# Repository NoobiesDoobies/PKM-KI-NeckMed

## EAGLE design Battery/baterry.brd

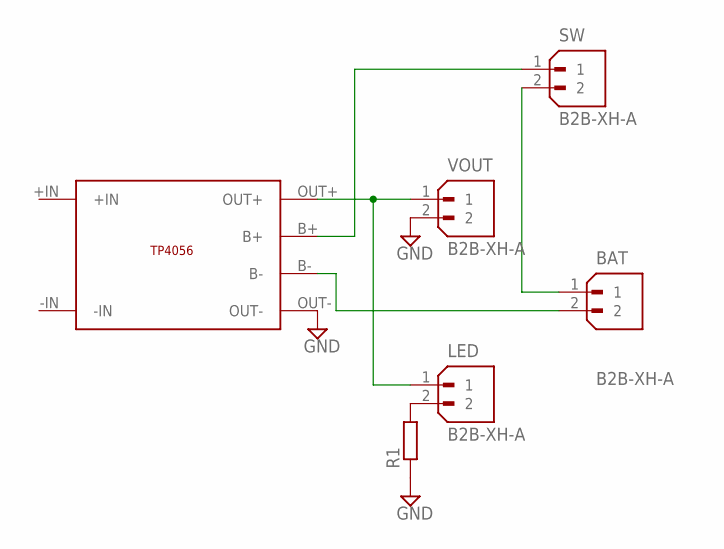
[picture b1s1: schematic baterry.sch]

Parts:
BAT: B2B-XH-A; JST_B2B-XH-A
LED: B2B-XH-A; JST_B2B-XH-A
R1: R-EU_0207/10; 0207/10
SW: B2B-XH-A; JST_B2B-XH-A
U$1: TP4056
VOUT: B2B-XH-A; JST_B2B-XH-A

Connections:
GND: R1.1, U$1.OUT-, VOUT.2
unnamed: LED.2, R1.2
unnamed: BAT.1, SW.2
unnamed: LED.1, U$1.OUT+, VOUT.1
unnamed: SW.1, U$1.B+
unnamed: BAT.2, U$1.B-

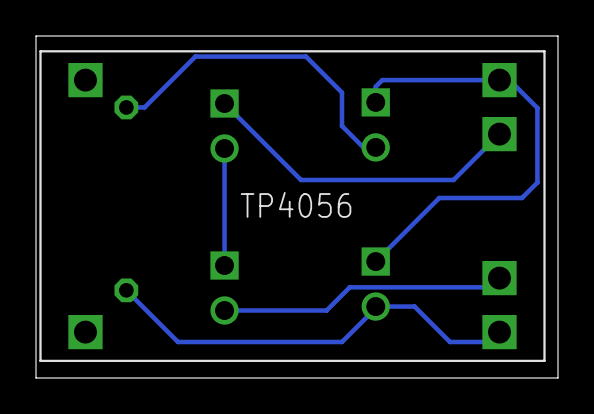
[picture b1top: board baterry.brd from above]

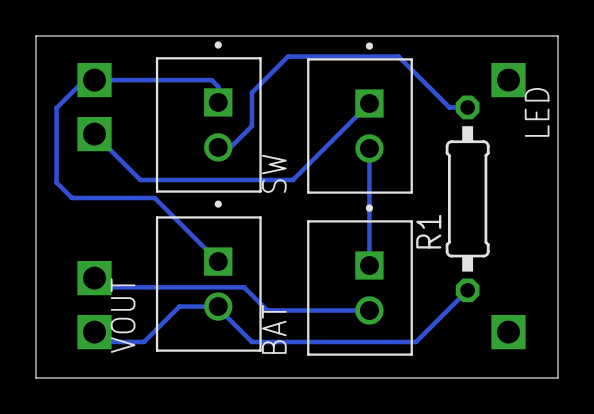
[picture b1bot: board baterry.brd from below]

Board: 2 copper layers, 29.0 x 19.0 mm, 6 parts (5 on the bottom side), 6 nets.

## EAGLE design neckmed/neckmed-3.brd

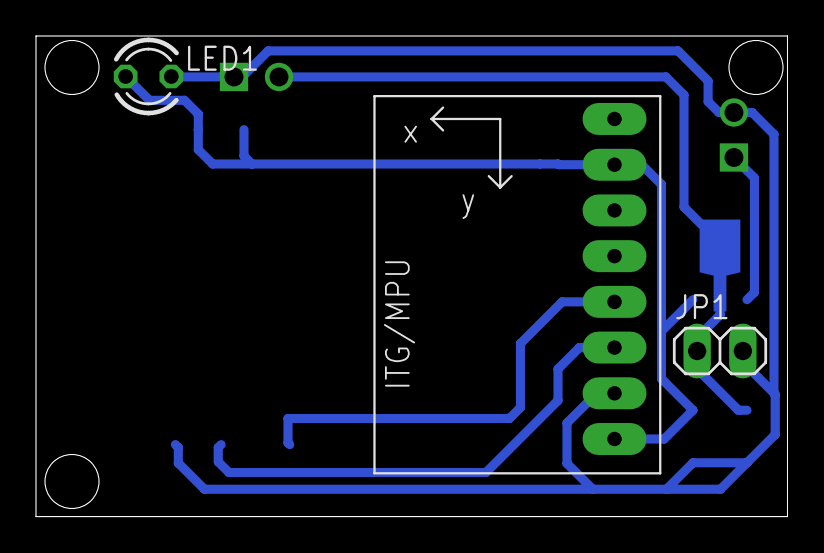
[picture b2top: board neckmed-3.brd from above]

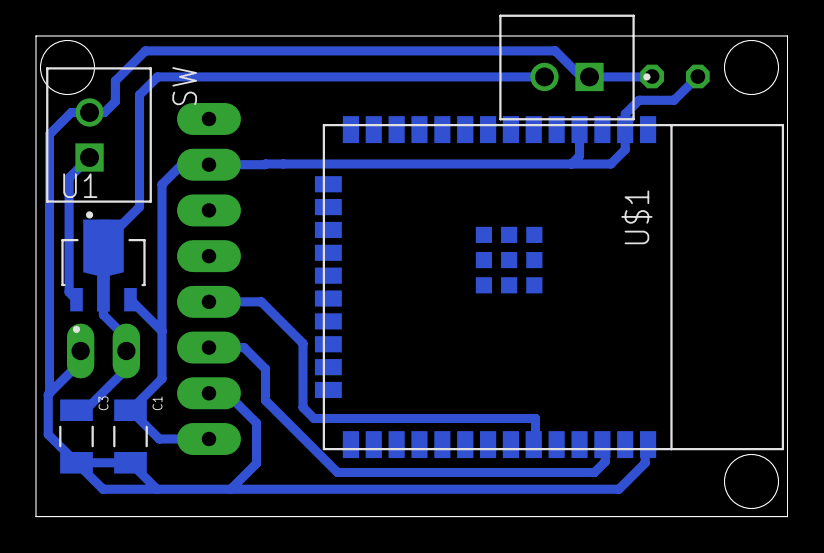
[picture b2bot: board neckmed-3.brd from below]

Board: 2 copper layers, 41.8 x 26.7 mm, 9 parts (6 on the bottom side), 6 nets.

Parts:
C1, C3: CL31B106KAHNNNE; CAPC3216X180N
CHARGER: B2B-XH-A; JST_B2B-XH-A
JP1: 1X02
LED1: TLLR4400; LED3MM
SW: B2B-XH-A; JST_B2B-XH-A
U1: HT7333; IC_HT7333
U2: GY-521MPU6050; GY-521
U$1: ESP32-WROOM-32E

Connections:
GND: C1.2, C3.2, CHARGER.1, JP1.2, LED1.K, SW.2, U2.GND, U$1.38
unnamed: C3.1, CHARGER.2, JP1.1, U1.2
unnamed: SW.1, U1.1
unnamed: U2.SCL, U$1.36
unnamed: U2.SDA, U$1.33
VCC: C1.1, LED1.A, U1.3, U2.ADO, U2.VCC, U$1.2, U$1.4

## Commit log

2023-07-05 add mounting for sensors
2023-09-26 add firmware for reading sensor and interacting with app through bluetooth
2023-09-26 tabbing
2023-10-07 add count duration functionality
2023-11-14 add pcb
2023-11-15 upload battery
2023-11-15 add lib
2023-11-16 add board pak eko
2023-11-16 done pcb
2023-11-16 minus esp clearance
2023-11-16 move switch
2023-11-19 update mpu drill diameter to 40 mil
2023-11-19 update xh library
2023-11-21 add charger CAD
2023-11-23 separate calibration characteristic
2023-11-23 change to only one characteristic
2023-11-24 add search for mpu
